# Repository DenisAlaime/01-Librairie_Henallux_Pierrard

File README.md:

# 01-Librairie_Henallux_Pierrard
Librairie Kicad ISI Pierrard Virton avec un projet type pour un démarrage facile.

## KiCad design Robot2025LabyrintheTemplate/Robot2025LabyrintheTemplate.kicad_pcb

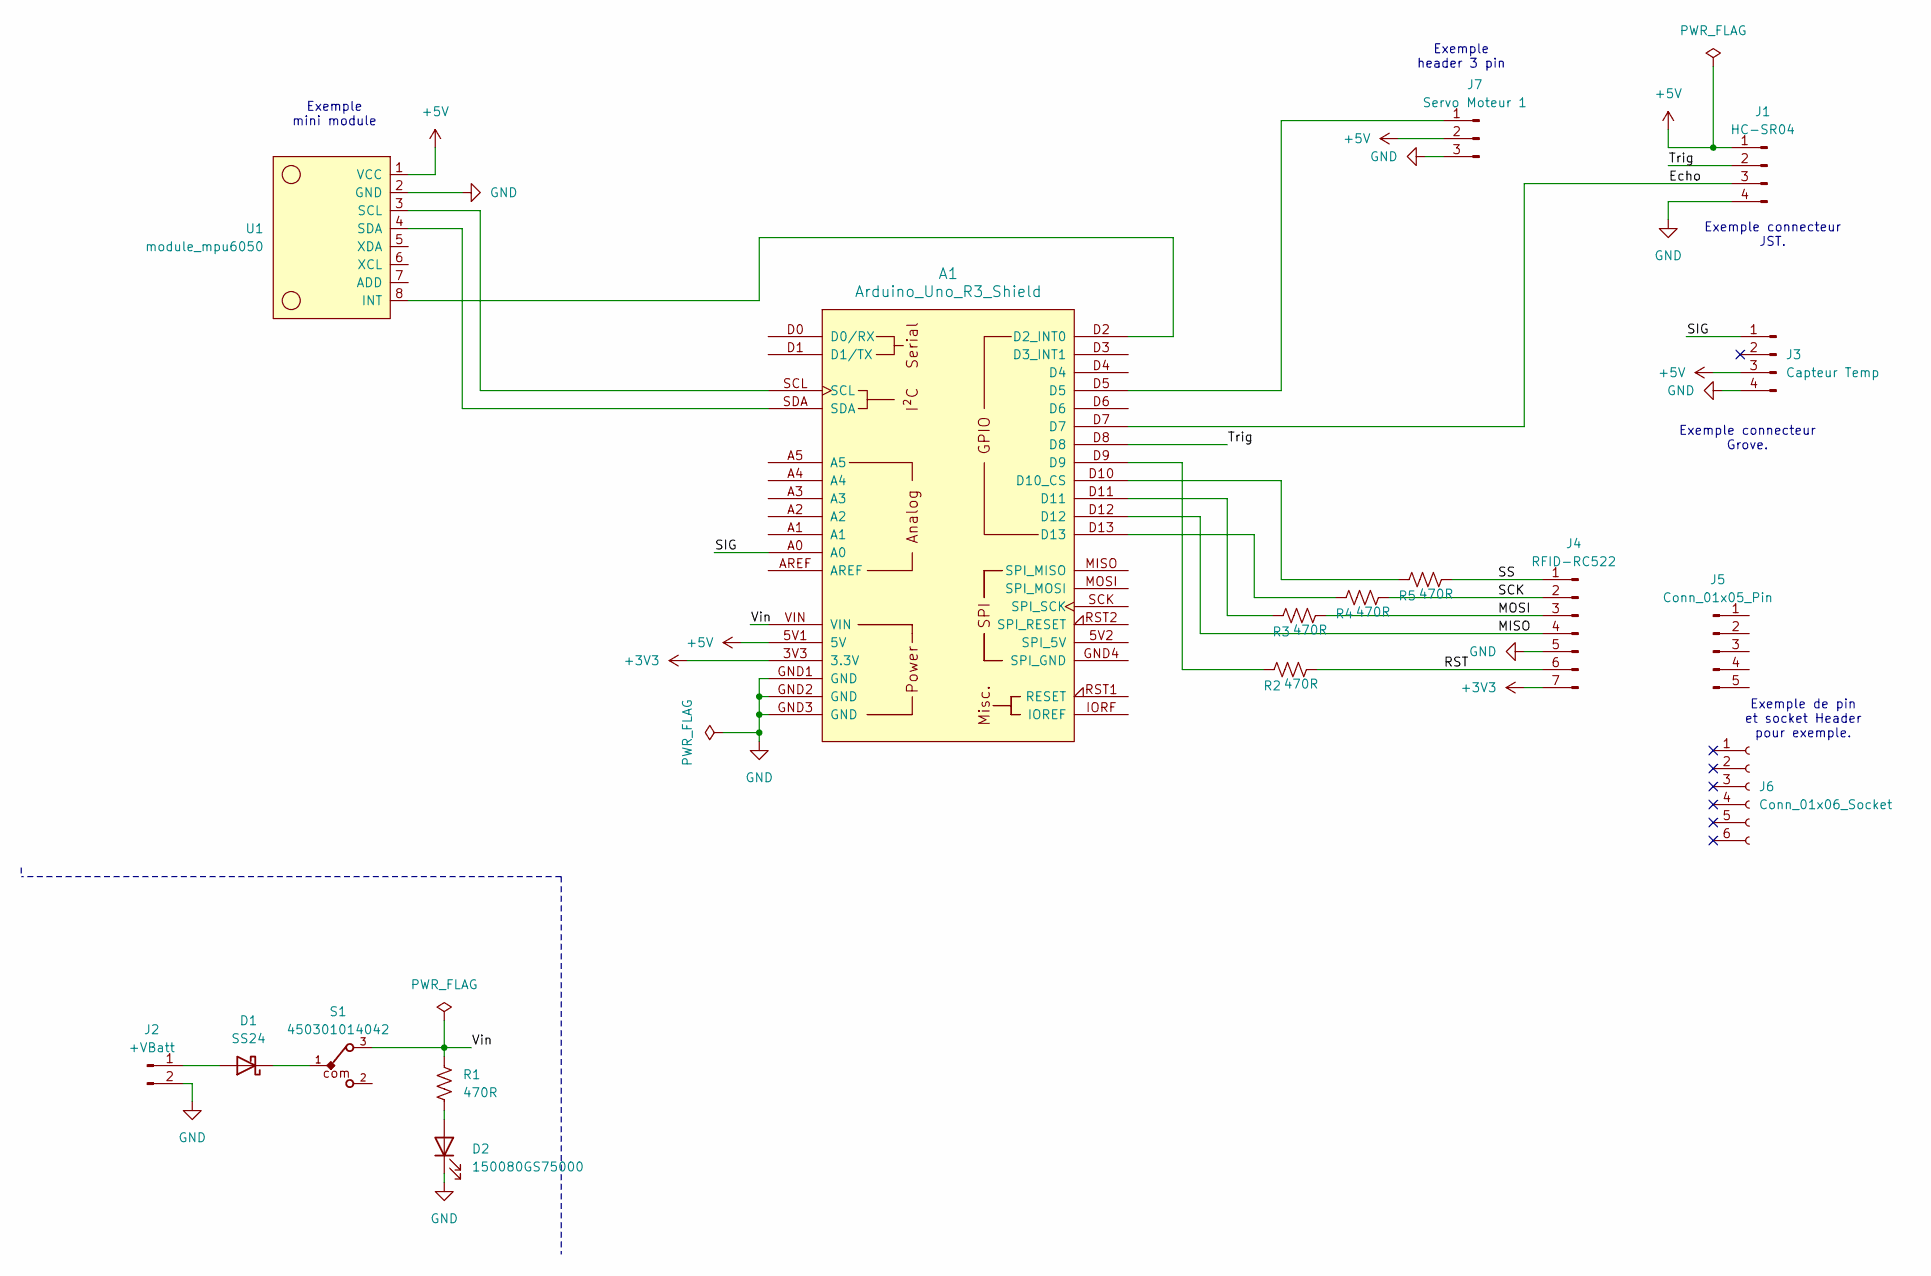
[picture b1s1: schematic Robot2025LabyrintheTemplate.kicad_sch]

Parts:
A1: Arduino_Uno_R3_Shield; Arduino_Uno_R3_Shield_LonPad
D1: SS24; D_SMB_Handsoldering
D2: 150080GS75000; LED_0805_2012Metric_Pad1.15x1.40mm_HandSolder
J1: HC-SR04; JST_XH_B4B-XH-AM_1x04_P2.50mm_Long_Vertical
J2: +VBatt; JST_XH_B2B-XH-AM_1x02_P2.50mm_Long_Vertical
J3: Capteur Temp; SEEED_Grove_110990030
J4: RFID-RC522; JST_XH_B7B-XH-AM_1x07_P2.50mm_Long_Vertical
J5: Conn_01x05_Pin; PinHeader_1x05_P2.54mm_Long_Vertical
J6: Conn_01x06_Socket; PinSocket_1x06_P2.54mm_Long_Vertical
J7: Servo Moteur 1; PinHeader_1x03_P2.54mm_Long_Vertical
R1, R2, R3, R4, R5: 470R; R_1206_3216Metric_Pad1.30x1.75mm_HandSolder
S1: 450301014042
U1: module_mpu6050

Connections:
+3V3: A1.3V3 (3.3V), J4.7
+5V: A1.5V1 (5V), J1.1, J3.3, J7.2, U1.1 (VCC)
/Echo: A1.D7, J1.3
/MISO: A1.D12, J4.4
/MOSI: J4.3, R3.2
/RST: J4.6, R2.2
/SCK: J4.2, R4.2
/SIG: A1.A0, J3.1
/SS: J4.1, R5.2
/Trig: A1.D8, J1.2
/Vin: A1.VIN, R1.1, S1.3
GND: A1.GND1 (GND), A1.GND2 (GND), A1.GND3 (GND), D2.1 (K), J1.4, J2.2, J3.4, J4.5, J7.3, U1.2 (GND)
unnamed: A1.D2 (D2_INT0), U1.8 (INT)
unnamed: A1.D10 (D10_CS), R5.1
unnamed: A1.D9, R2.1
unnamed: A1.D11, R3.1
unnamed: A1.D13, R4.1
unnamed: D1.2 (A), J2.1
unnamed: D1.1 (K), S1.1
unnamed: D2.2 (A), R1.2
unnamed: A1.D5, J7.1
unnamed: A1.SCL, U1.3 (SCL)
unnamed: A1.SDA, U1.4 (SDA)

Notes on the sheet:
Exemple mini module
Exemple connecteur JST.
Exemple connecteur Grove.
Exemple header 3 pin
Exemple de pin et socket Header pour exemple.

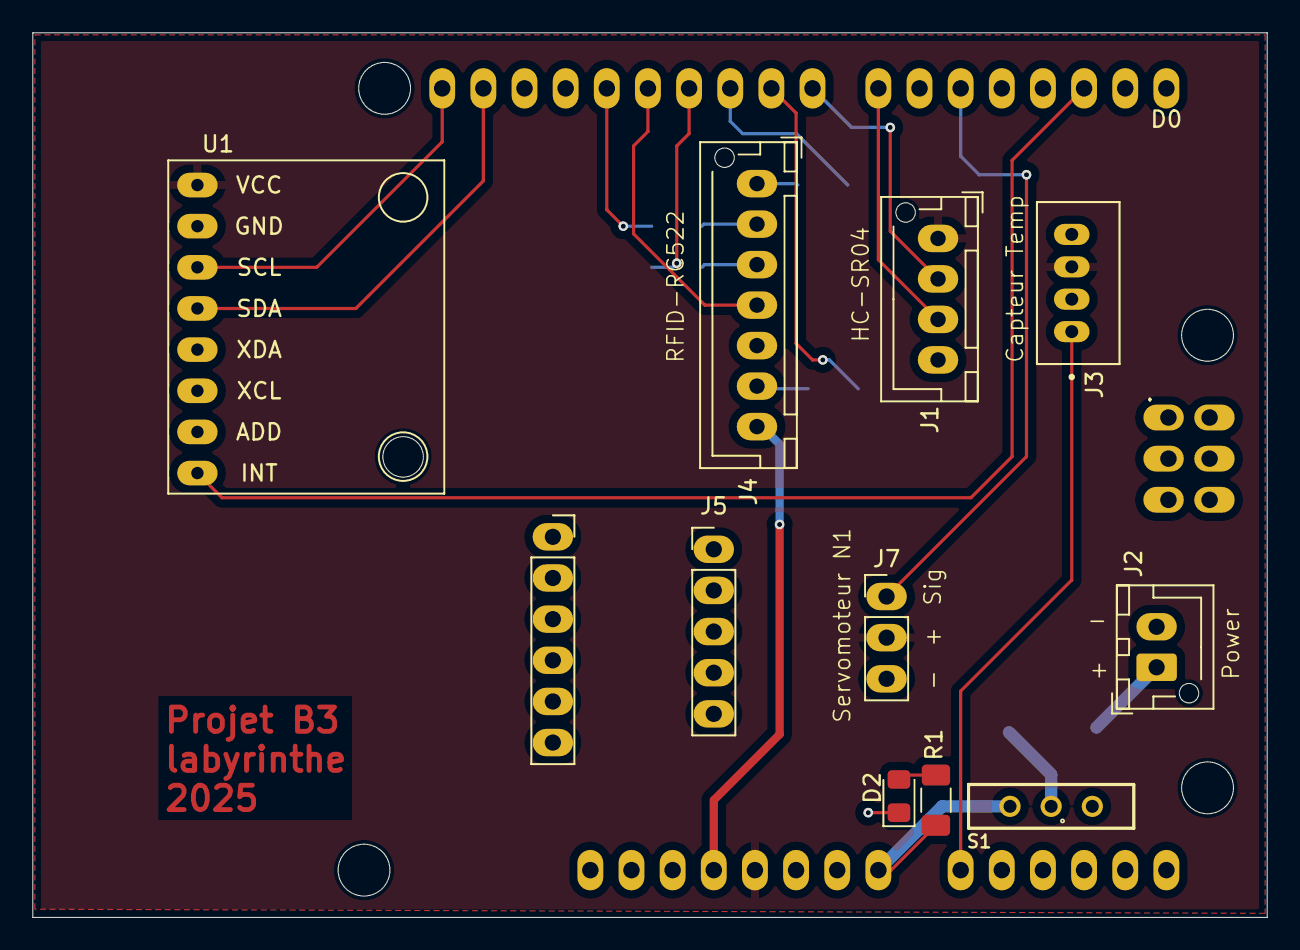
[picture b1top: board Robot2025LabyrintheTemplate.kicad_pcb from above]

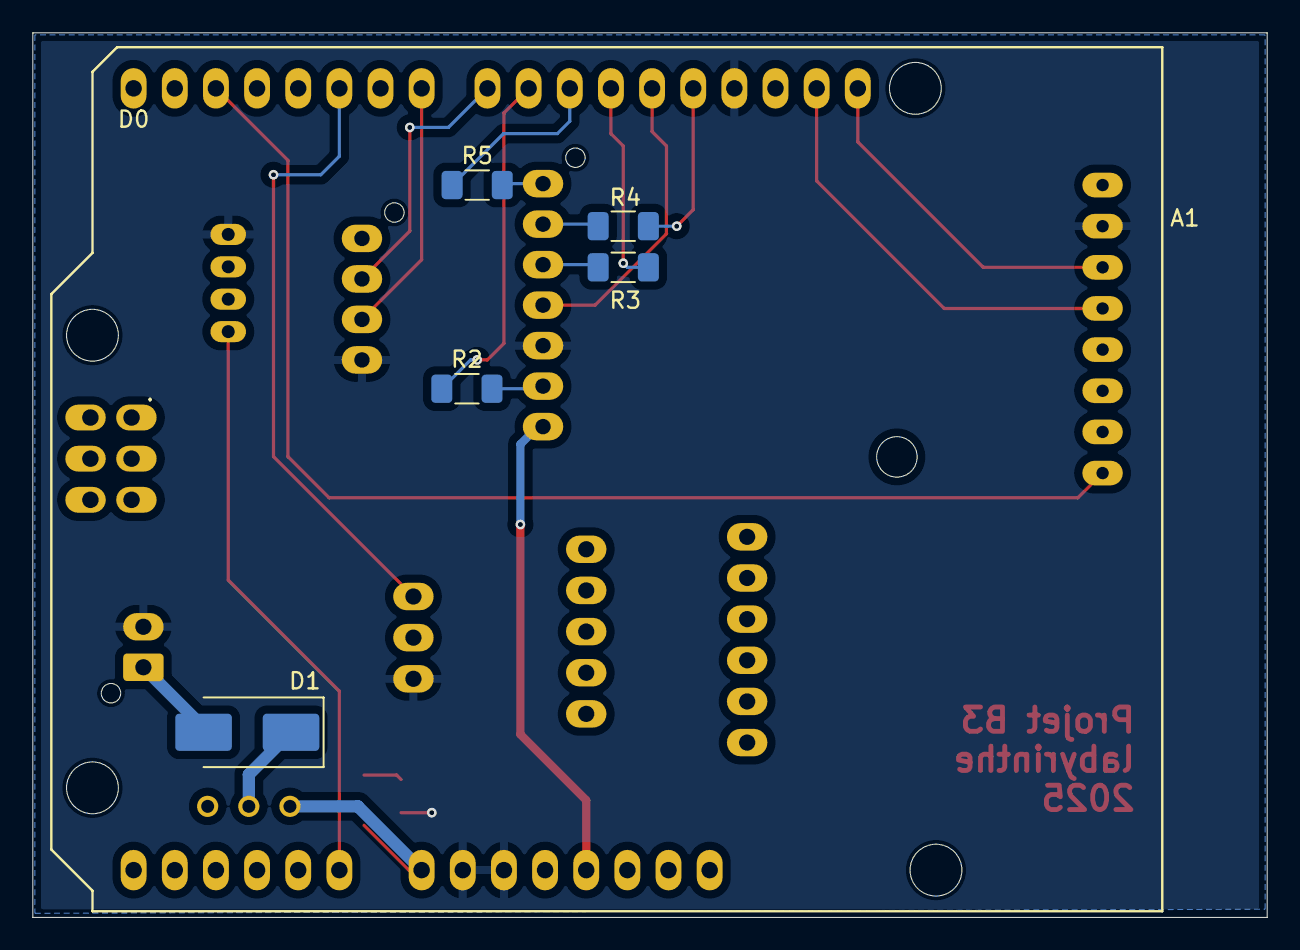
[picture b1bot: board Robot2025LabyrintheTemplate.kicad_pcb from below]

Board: 2 copper layers, 76.2 x 54.6 mm, 17 parts (5 on the bottom side), 23 nets.

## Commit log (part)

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2025-03-18 Premier commit, ajout des composants de base
2025-03-19 Grand néttoyage, et passage en revue des différents composants Modificaton du chemin vers les composants 3d, kicad 8 vers kicad 9 Modifivations diverses.
2025-03-19 Nettoyage, optimisation
2025-03-20 Ajout de quelques composants, nettoyage .
2025-03-20 Suppression des fichiers .bak
2025-03-20 .gitignore is now working
2025-03-20 Juste un petit test pour vérifier le fonctionnement du gitigore
2025-03-20 Ajout d'un projet Template pour un démarrage facile pour les étudiants.
2025-03-20 Update README.md
    Modification du fichier readme
2025-03-20 Suppression de la librairie Pierrard Virton, plus utilisée
2025-04-03 Ajout d'un module dans la lib: TCA9548A qui une carte de Adafruit pour augmenter le nombre de lignes I2C
2025-05-07 Ajout de nouvelles empreintes, correction importante sur le symbole arduino mega, c'était une mauvaise verion qui n'a rien à voir avec le Mega Normal c'est le symbole du clone :https://fr.aliexpress.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
2025-05-13 Ajout d'un connecteur Wurth "691321300004" série 321 pad de 3.81mm
2025-05-18 Ajout de modules: Adafruit 3648 SEN-13879 Ajout du step pour arduino Mega
2025-06-07 Ajout d'un connecteur wurth
2025-07-09 Ajout d'empreintes 3D LED 0805-1206 Wurth
2025-08-22 Ajout de composants
2025-09-16 Ajout de composants présent dans inventree
2025-09-21 Ajout symboles carte corde vibrante
2025-09-22 Modification silscreen led 3mm (problème avec de DRC)
2025-09-23 Ajout composants driver Shell Eco
2025-10-07 Ajout composants
2025-10-16 Hugo : ajout module GPS NEO M9N
2025-10-23 Hugo : ajout module BME280
2025-10-31 Ajout du transistor NDT3055L
2025-11-02 Ajout de composants pour le projet corde vibrante
2025-11-07 ajout de différents composants en provenance des étudiants
2025-11-18 Ajout footprint PI4
2025-11-18 Ajout composants pour la corde vibrante
2025-11-19 Ajout de composants pour correspondre à Inventree
2025-11-26 Adaptation des propriétés pour uniformiser les bibliothèques
2025-11-26 Uniformisation des propriétés des composants
2026-01-03 ajout Diodes
2026-02-10 Ajout connecteurs
2026-02-21 Ajout diode 1n4001
2026-03-30 Ajout module ESP32
2026-04-01 Ajout d'un fusible format voiture et d'un convertisseur DC-DC
2026-04-07 Ajout ESP32-S3 DevKitC-1
2026-04-08 Ajout de modules RF nrf24L1
2026-04-10 Ajout driver stepper TMC2208 + ESP32-S3
2026-04-12 Modificatin de l'empreint pour le module DC-DC Df robot
2026-04-22 Ajout de différents composants et empreintes 3D
